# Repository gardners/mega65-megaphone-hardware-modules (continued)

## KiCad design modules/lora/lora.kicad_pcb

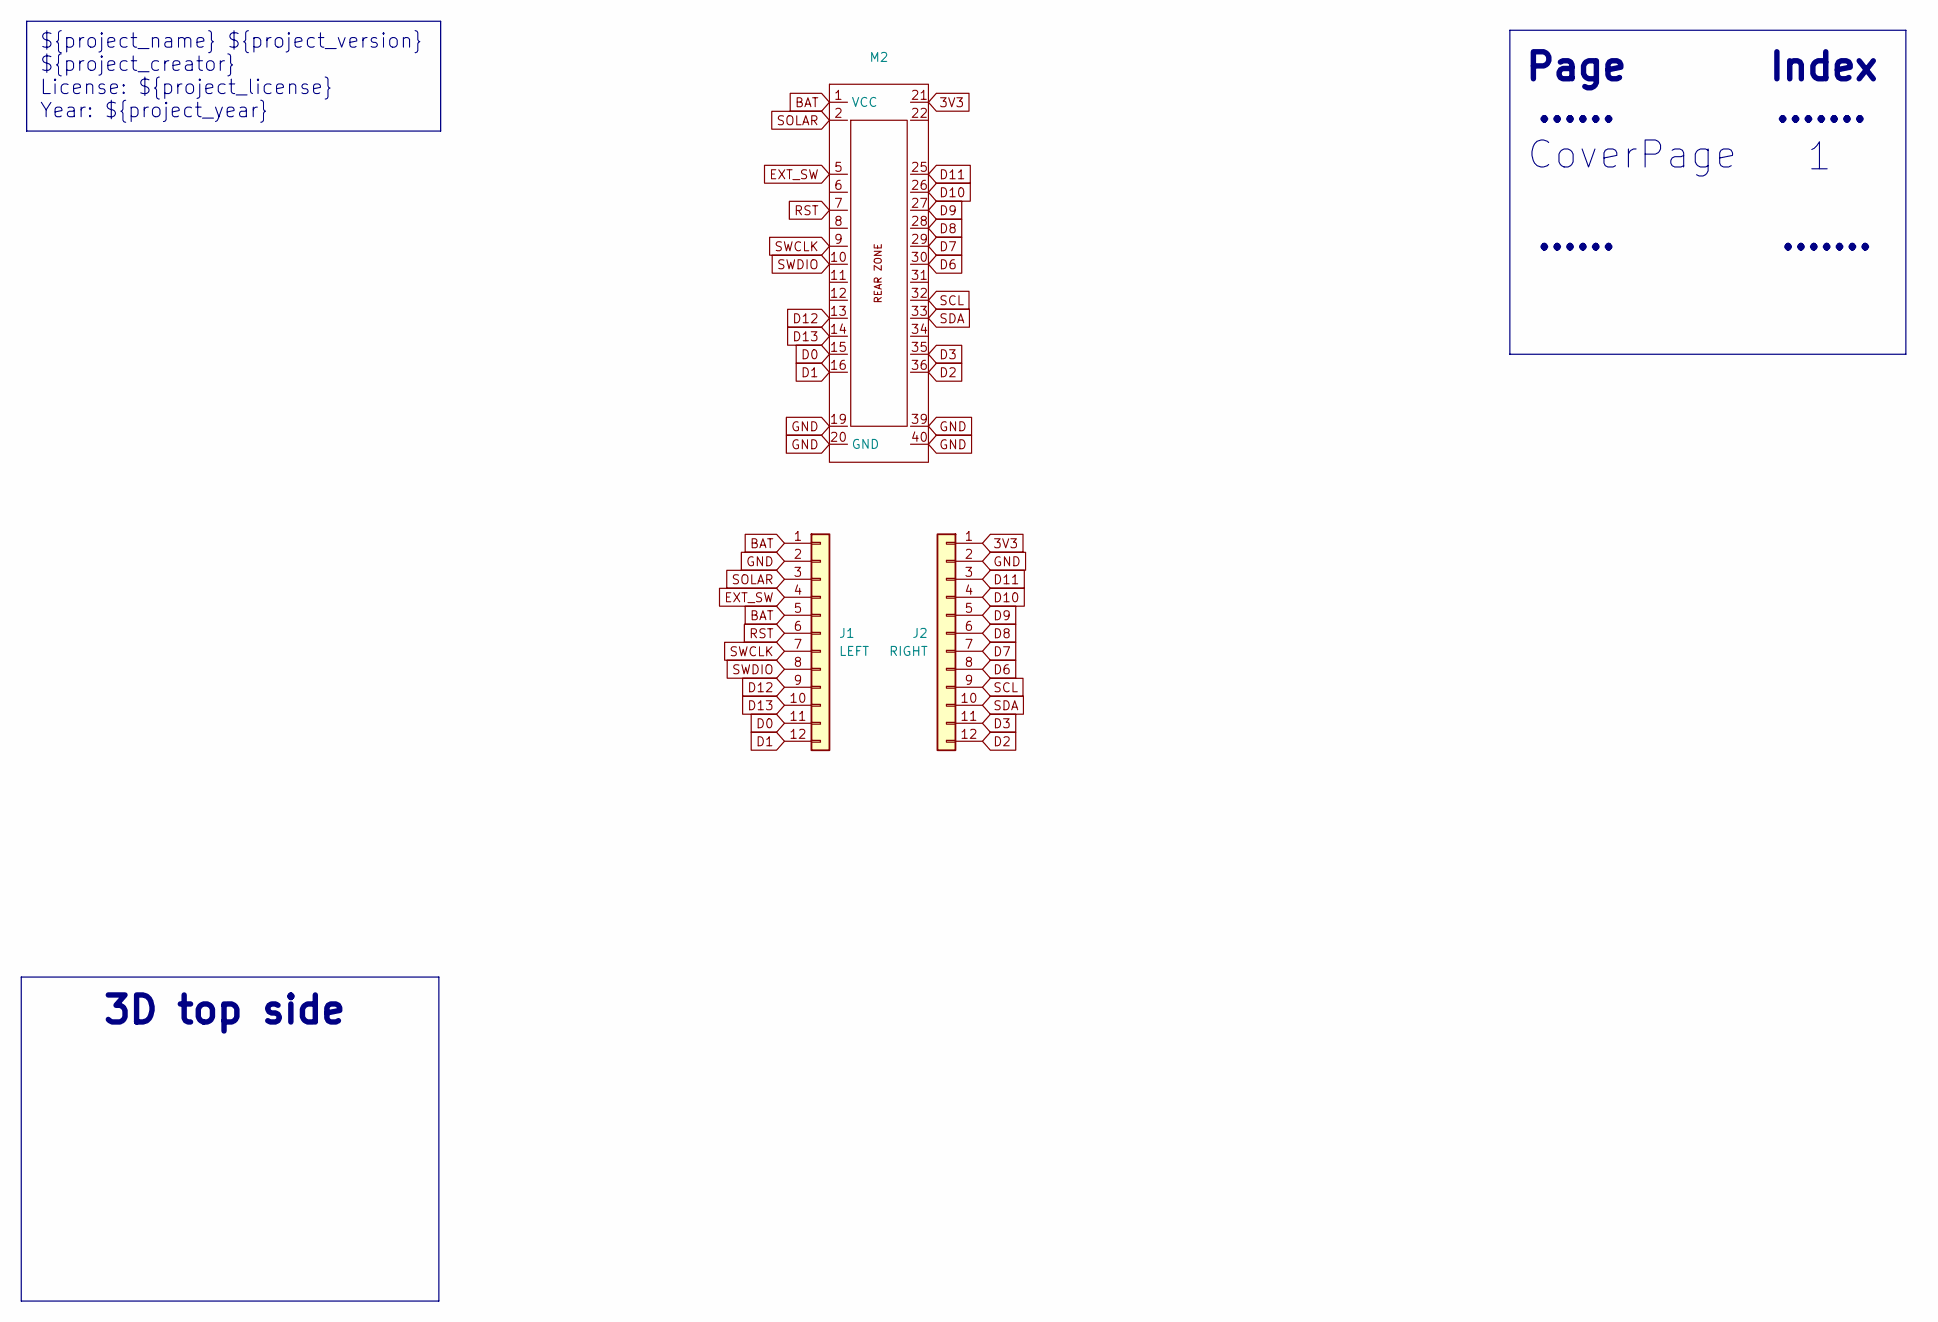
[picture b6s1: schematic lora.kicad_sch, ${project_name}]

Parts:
J1: LEFT; PinSocket_1x12_P2.54mm_Vertical
J2: RIGHT; PinSocket_1x12_P2.54mm_Vertical
M2: MegaCastle2x20-Module-I40.0x46.0-MBCFFF3CFFF3-SPAREPAD

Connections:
3V3: J2.1, M2.21
BAT: J1.1, J1.5, M2.1 (VCC)
D0: J1.11, M2.15
D1: J1.12, M2.16
D2: J2.12, M2.36
D3: J2.11, M2.35
D6: J2.8, M2.30
D7: J2.7, M2.29
D8: J2.6, M2.28
D9: J2.5, M2.27
D10: J2.4, M2.26
D11: J2.3, M2.25
D12: J1.9, M2.13
D13: J1.10, M2.14
EXT_SW: J1.4, M2.5
GND: J1.2, J2.2, M2.19, M2.20 (GND), M2.39, M2.40
RST: J1.6, M2.7
SCL: J2.9, M2.32
SDA: J2.10, M2.33
SOLAR: J1.3, M2.2
SWCLK: J1.7, M2.9
SWDIO: J1.8, M2.10

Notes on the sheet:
3D top side
......
CoverPage
${project_name} ${project_version} ${project_creator} License: ${project_license} Year: ${project_year}
Page
.......
Index

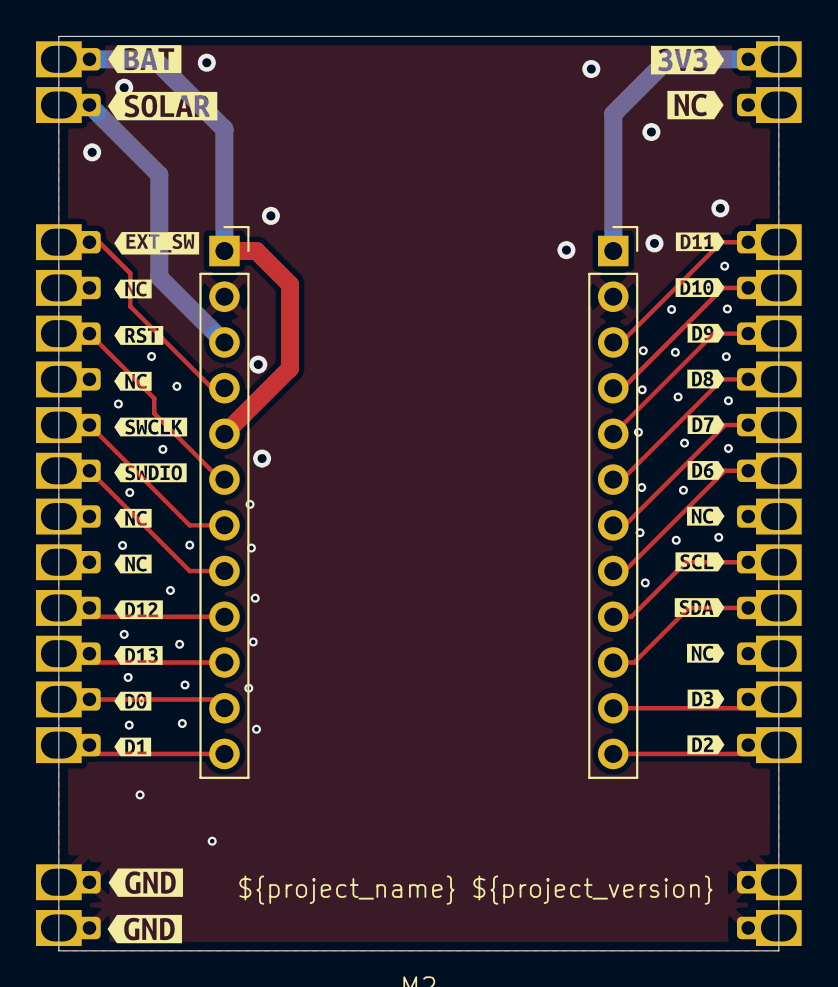
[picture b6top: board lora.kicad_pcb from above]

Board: 2 copper layers, 40.0 x 50.8 mm, 33 parts (0 on the bottom side), 22 nets.

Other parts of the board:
kibuzzard-69131C8F: G***; kibuzzard-69131C8F
kibuzzard-69131C88: G***; kibuzzard-69131C88
kibuzzard-69131C99: G***; kibuzzard-69131C99
kibuzzard-69131CA1: G***; kibuzzard-69131CA1
kibuzzard-69131CAF: G***; kibuzzard-69131CAF
kibuzzard-69131CB5: G***; kibuzzard-69131CB5
kibuzzard-69131CBD: G***; kibuzzard-69131CBD
kibuzzard-69131CC2: G***; kibuzzard-69131CC2
kibuzzard-69131CC9: G***; kibuzzard-69131CC9
kibuzzard-69131CCF: G***; kibuzzard-69131CCF
kibuzzard-69131CD4: G***; kibuzzard-69131CD4
kibuzzard-69131CD9: G***; kibuzzard-69131CD9
kibuzzard-69131D58: G***; kibuzzard-69131D58
kibuzzard-69131D76: G***; kibuzzard-69131D76
kibuzzard-691317B6, kibuzzard-691317B6#2: G***; kibuzzard-691317B6
kibuzzard-691318A4: G***; kibuzzard-691318A4
kibuzzard-691318AC: G***; kibuzzard-691318AC
kibuzzard-691318B3: G***; kibuzzard-691318B3
kibuzzard-691318BA: G***; kibuzzard-691318BA
kibuzzard-691318BF: G***; kibuzzard-691318BF
kibuzzard-691318C6: G***; kibuzzard-691318C6
kibuzzard-691318CD: G***; kibuzzard-691318CD
kibuzzard-691318D3: G***; kibuzzard-691318D3
kibuzzard-6913178F1: G***; kibuzzard-6913178F
kibuzzard-6913188E: G***; kibuzzard-6913188E
kibuzzard-6913189D: G***; kibuzzard-6913189D
kibuzzard-69131742: G***; kibuzzard-69131742
kibuzzard-69131759: G***; kibuzzard-69131759
kibuzzard-69131896: G***; kibuzzard-69131896

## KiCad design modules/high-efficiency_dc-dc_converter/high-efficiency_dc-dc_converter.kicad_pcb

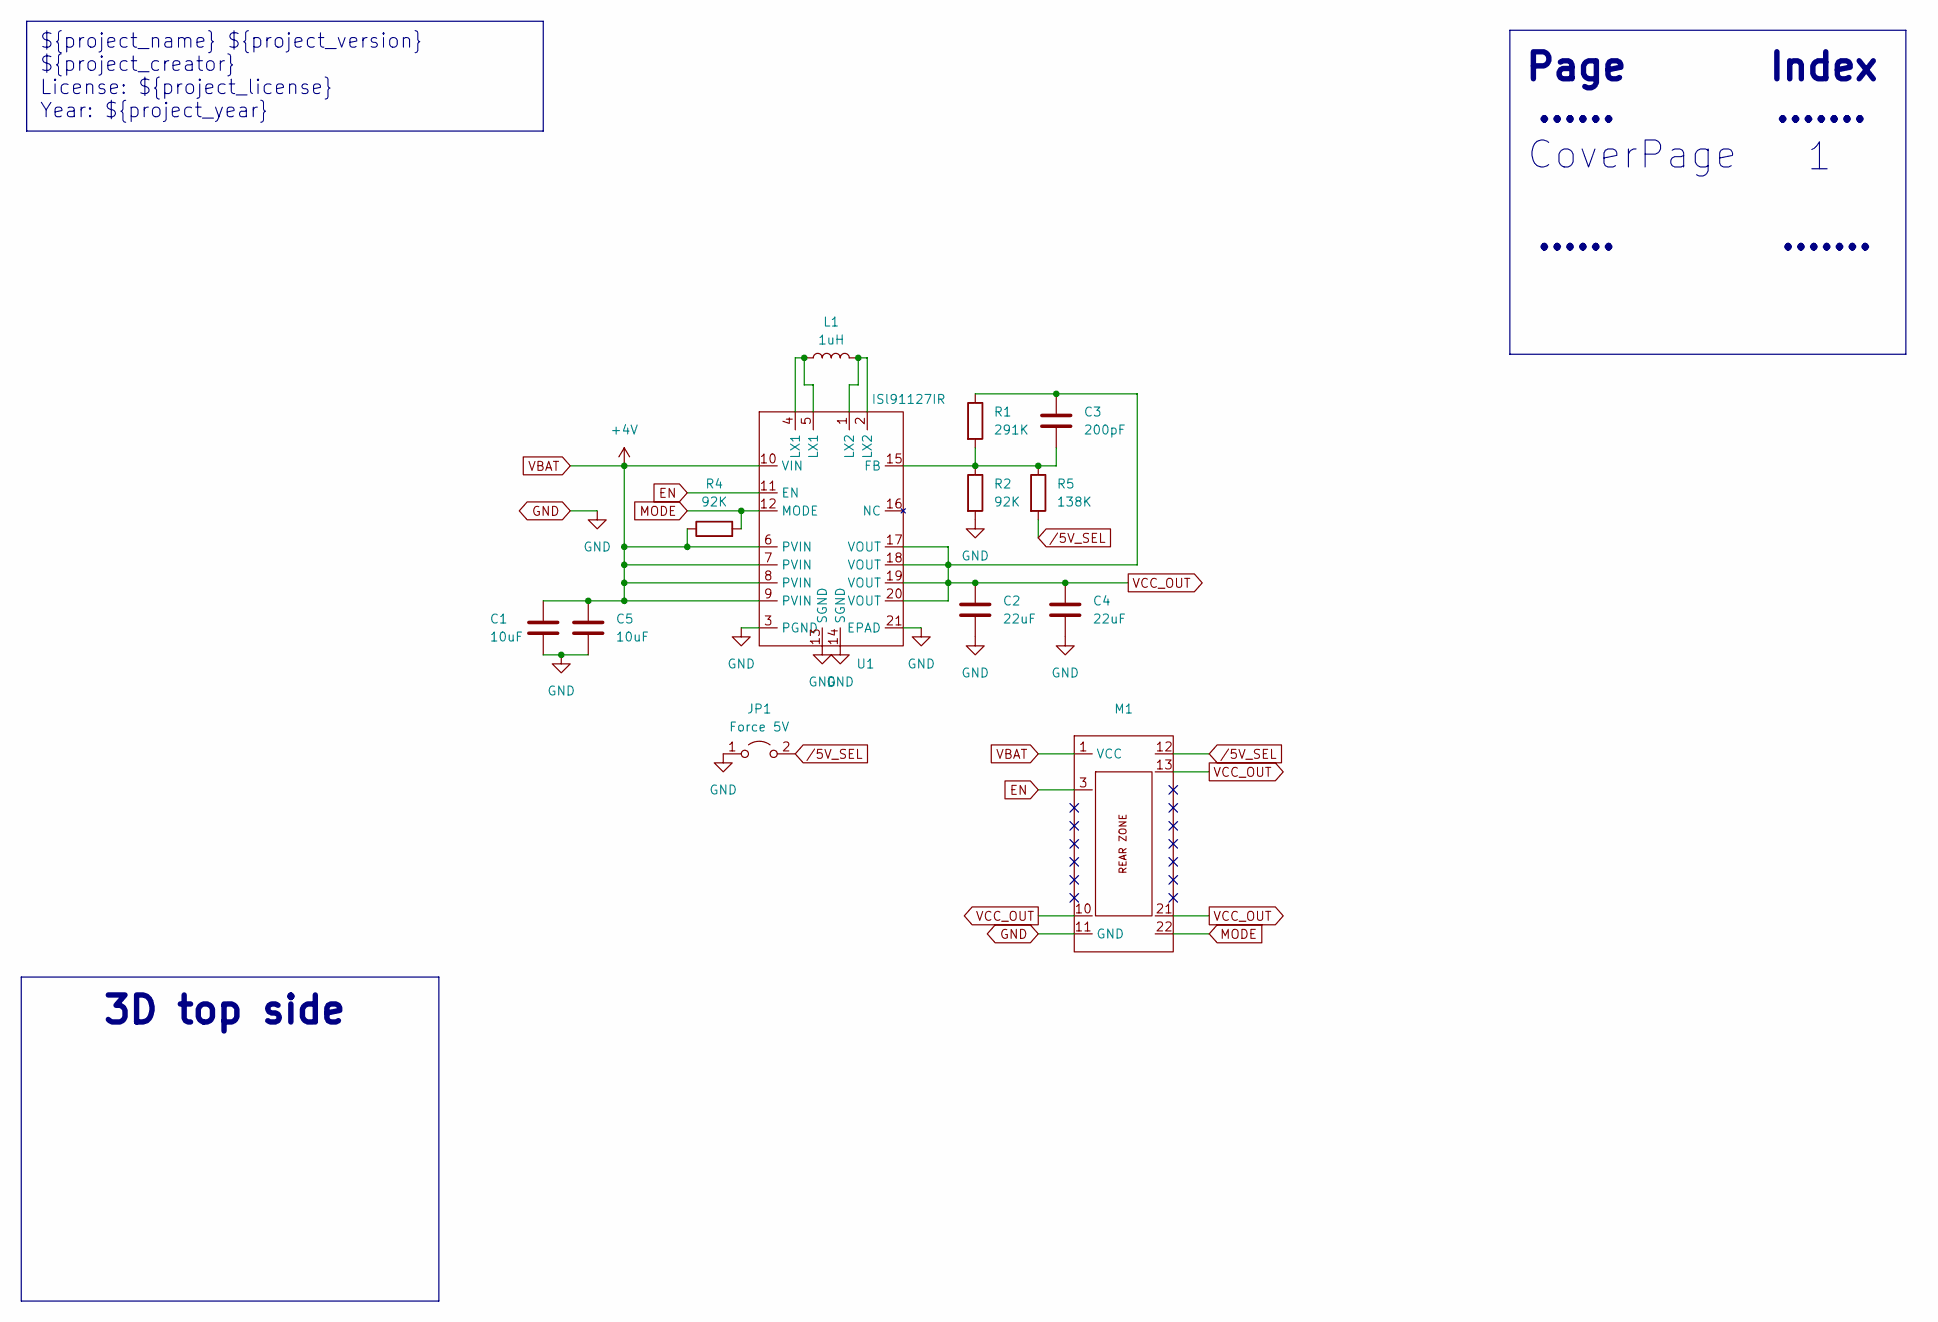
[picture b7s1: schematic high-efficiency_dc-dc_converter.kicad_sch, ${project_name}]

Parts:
C1, C5: 10uF; C_0805_2012Metric; Mouser PN 187-CL21A106KOQNNNG
C2, C4: 22uF; C_0805_2012Metric; Mouser PN 187-CL21A226KOQNNNG
C3: 200pF; C_0805_2012Metric; Mouser 603-CC805JRNPO9BN201
JP1: Force 5V; SolderJumper-2_P1.3mm_Open_RoundedPad1.0x1.5mm
L1: 1uH; L_1008_2520Metric; Mouser PN 81-DFE252012P-1R0MP2
M1: MegaCastle2x11-Module-I15.7x23.1-MA0780C-SPAREPAD
R1: 291K; R_0603_1608Metric
R2, R4: 92K; R_0603_1608Metric; Mouser PN 603-RC0603FR-0791KL
R5: 138K; R_0603_1608Metric; Mouser PN 660-RK73H1JTTD1403F
U1: ISl91127IR; QFN50P400X400X90-21N; Mouser PN 968-ISL91127IRAZ-T

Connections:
EN: M1.3, U1.11 (EN)
GND: C1.2, C2.2, C4.2, C5.2, JP1.1 (A), M1.11 (GND), R2.2, U1.3 (PGND), U1.13 (SGND), U1.14 (SGND), U1.21 (EPAD)
MODE: M1.22, R4.2, U1.12 (MODE)
unnamed: L1.1, U1.4 (LX1), U1.5 (LX1)
unnamed: L1.2, U1.1 (LX2), U1.2 (LX2)
unnamed: C3.2, R1.2, R2.1, R5.1, U1.15 (FB)
VBAT: C1.1, C5.1, M1.1 (VCC), R4.1, U1.6 (PVIN), U1.7 (PVIN), U1.8 (PVIN), U1.9 (PVIN), U1.10 (VIN)
VCC_OUT: C2.1, C3.1, C4.1, M1.10, M1.13, M1.21, R1.1, U1.17 (VOUT), U1.18 (VOUT), U1.19 (VOUT), U1.20 (VOUT)
/5V_SEL: JP1.2 (B), M1.12, R5.2

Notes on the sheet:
3D top side
......
CoverPage
${project_name} ${project_version} ${project_creator} License: ${project_license} Year: ${project_year}
Page
.......
Index

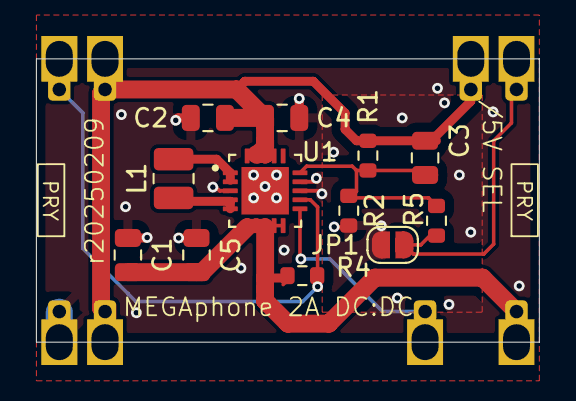
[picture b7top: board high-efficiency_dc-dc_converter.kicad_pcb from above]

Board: 2 copper layers, 27.9 x 15.7 mm, 13 parts (1 on the bottom side), 9 nets.

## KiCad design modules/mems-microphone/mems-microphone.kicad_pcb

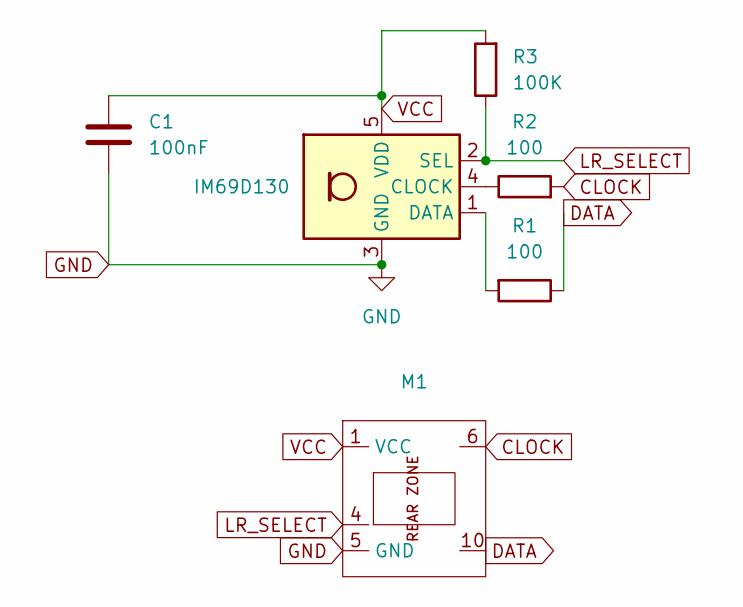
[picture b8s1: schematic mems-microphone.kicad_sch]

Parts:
C1: 100nF; C_1206_3216Metric; Mouser PN 581-12066D104KAT4A
M1: MegaCastle2x5-Module-I10.0x7.9-M9C4-SPAREPAD
MK1: IM69D130; Knowles_LGA-5_3.5x2.65mm; Mouser PN 726-IM69D130V01XTSA1
R1: 100; R_0603_1608Metric; Mfr. PN AC0603JR-07100RL; Mouser PN 603-AC0603JR-07100RL
R2: 100; R_0603_1608Metric; Mouser PN 603-AC0603JR-07100RL
R3: 100K; R_0603_1608Metric; Mouser PN 603-AC0603JR-07100KL

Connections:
CLOCK: M1.6, R2.2
DATA: M1.10, R1.1
GND: C1.2, M1.5 (GND), MK1.3 (GND)
LR_SELECT: M1.4, MK1.2 (SEL), R3.1
unnamed: MK1.4 (CLOCK), R2.1
unnamed: MK1.1 (DATA), R1.2
VCC: C1.1, M1.1 (VCC), MK1.5 (VDD), R3.2

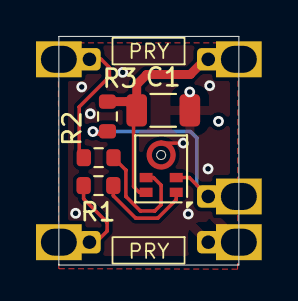
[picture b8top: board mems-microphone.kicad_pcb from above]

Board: 2 copper layers, 10.0 x 12.7 mm, 6 parts (1 on the bottom side), 7 nets.

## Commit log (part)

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2025-11-07 begin creating module status table
2025-11-07 fix empty columns
2025-11-07 populate remainder of status
2025-11-10 Moving all modulles to modules folder
2025-11-10 Adding link
2025-11-10 Updating links
2025-11-10 Adding auto export
2025-11-10 adding output.kibot
2025-11-10 workflow update
2025-11-10 Update one board - checking workflow
2025-11-10 Updating workflow to detect kicad changes
2025-11-10 Update production files [skip ci]
2025-11-10 Readme update, adding pictures of assembled modules
2025-11-10 Updating all modules
2025-11-10 Updating lora module
2025-11-10 Adding License for all modules
2025-11-10 Updating all schematics
2025-11-10 Updating schematics
2025-11-11 Manually do action
2025-11-11 Adding LoRa module
2025-11-11 mppt charge
2025-11-12 update status
2025-11-12 Initial carier board
2025-11-12 fixing main-carrier
2025-11-13 connecting power
2025-11-13 Baseboard SCH update
2025-11-15 Adding icesugar module - placing Ice sugar on base board, remove FPGA as module, add FPGA directly
2025-11-24 Routing
2025-11-25 Fully routing base board
